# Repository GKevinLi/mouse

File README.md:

# Mouse: A custom wireless Bluetooth mouse

There is no cool name for it. I'm not good at naming things.

This is a wireless-capable Bluetooth mouse made entirely using custom parts. Everything required to make it is open source, and the files for each part are in their respective folders.
The only parts of this mouse that aren't custom are the battery and the various PCB attached components (switches, encoder, etc). 

This design can be used with any mouse switch, as long as it has dimensions of 12.8 x 5.8 x 6.5, and any 11mm mouse encoder. 6x6x7.3 silent switches theoretically should be able to work on this design as well, albeit with a few CAD modifications.

For more information on specific parts of the project, refer to the folder-specific READMEs in the cad, firmware, and pcb folders.\
CAD Readme: [Link](<https://github.com/GKevinLi/mouse/blob/main/cad/README.md>)\
Firmware Readme:  [Link](<https://github.com/GKevinLi/mouse/blob/main/firmware/README.md>)\
PCBs Readme:  [Link](<https://github.com/GKevinLi/mouse/blob/main/pcb/README.md>)

## Features

- PMW3610 Mouse Sensor
- nRF52833 Microcontroller
- Can be used when plugged in or on battery power
- Battery charging circuit
- Custom scroll wheel and mouse case
- 2 configurable side buttons

## Bill of Materials

| Item Name | Qty | Price (total) (USD) | Item link | Notes |
| --- | --- | --- | --- | --- |
| Mouse PCB, fully assembled | 2 | $150.05 | [Link](<https://jlcpcb.com/>) | this is how much it cost me for 5 PCBs, 2 fully assembled. Prices may vary. |
| PMW3610 | 1 | $1.09 | [Link](<https://www.aliexpress.us/item/3256809533648177.html?spm=a2g0o.productlist.main.7.117e61f1qj4GGu&algo_pvid=bf3782c9-0cfd-42bd-8a3f-8618d8d4e2c6&algo_exp_id=bf3782c9-0cfd-42bd-8a3f-8618d8d4e2c6-6&pdp_ext_f=%7B%22order%22%3A%22116%22%2C%22eval%22%3A%221%22%2C%22fromPage%22%3A%22search%22%7D&pdp_npi=6%40dis%21USD%214.53%211.09%21%21%214.53%211.09%21%402101e7a317932458066444948e0f08%2112000049947017292%21sea%21US%210%21ABX%211%210%21n_tag%3A-29910%3Bd%3A2859b2dd%3Bm03_new_user%3A-29895%3BpisId%3A5000000218152484&curPageLogUid=guoUMjTe3YSZ&utparam-url=scene%3Asearch%7Cquery_from%3A%7Cx_object_id%3A1005009719962929%7C_p_origin_prod%3A&_gl=1*7xkuy0*_gcl_au*MTIzNTAwODMyMy4xNzkzMjQ1ODEw*_ga*ODkxNjEwMTMuMTc5MzI0NTgxMg..*_ga_VED1YSGNC7*czE3OTMyNDU4MTEkbzEkZzAkdDE3OTMyNDU4MTEkajYwJGwwJGgw>) | this price is with the aliexpress welcome deal |
| Mouse Switch | 5 | $3.95 | [Link](<https://www.digikey.com/en/products/detail/aratas-formerly-omron-components-/D2FC-F-7N(60M)/20484328?gclsrc=aw.ds&gad_source=1&gad_campaignid=20509826117&gbraid=0AAAAADrbLlg5bJviKM8Id0HjudlkVKetQ&gclid=CjwKCAjwuobXBhBXEiwAYUaIlcOEJucEfbAOKAHeb95FXKGvGlaxJ1Z_NS2kmmfVS1ARsBkzc0fthhoCX_oQAvD_BwE>) | Any 12.8x5.8x6.5 mouse switch works, you can buy them or take them off old mice |
| 11mm Mouse Encoder | 1 | $9.39 | [Link](<https://www.amazon.com/dp/B07HCFMQ3X?plpRedirect=mhFallback&ref=clp_hp_h_pc>) | Any 11mm mouse encoder works, you can buy them or take them off old mice |
| 602535 Battery | 1 | $7.99 | [Link](<https://www.amazon.com/dp/B0GWCRMPSY?plpRedirect=mhFallback&ref=clp_hp_h_pc>) | Any 602535 battery works here. |
| **Total Price (USD)** | | **$172.47** | | |

To build the mouse fully, you will need a soldering iron (and some soldering experience), an SWD debugger, and access to a 3D printer. The links given in the BOM are just recommendations. The battery is optional and the mouse can be used via USB power without it.

## Building tips / Notes:
- This project is currently in a very early stage of development, so building this is not recommended at this time. Only try to build this yourself if you REALLY know what you are doing. It is possible that your project may not work due to some oversight I haven't found yet.
- I am a very busy college student so updates on this may be slow.
- There are probably many issues with this design that I have not discovered yet. Documented issues will be in the folder-specific READMEs.
- The current board design has several major issues. These will have to either be fixed in KiCad or by modifying the assembled board. A corrected version of the design will be made.... eventually, but for now I have documented the issues in the PCB folder's readme file.
- The current mouse case does not have side buttons. These will be added later as well.
- The current mouse case does not support mouse skates.
- To build this, you will have to order your own boards from JLCPCB or another PCB manufacturer. Instructions for this will not be provided at the moment, since the board design has issues anyway. If you have enough experience to fix them then you probably have enough experience to order the boards by yourself as well.
- There is currently not a lot of documentation on this project. This is just a fun personal project of mine at the moment, and I do not have that much time to consistently work on it. I will update this in the future, though.
- THIS IS NOT (currently) A GOOD MOUSE. Do not expect this project, in its current form, to be better than whatever mouse you personally own.

## Credits:
https://github.com/badjeff/leylabella for CAD references

https://github.com/siderakb/pmw3610-pcb for a PMW3610 schematic reference

https://github.com/wareya/DIY-Gaming-Mouse for PCB design and CAD references

KiCanvas PCB Link Here:

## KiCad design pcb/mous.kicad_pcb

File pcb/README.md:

# Wireless Mouse PCB README

This is the README for the project's PCB and KiCad files. Relevant information and known issues will be documented here.
An update will be coming soon to fix the current issues.

## Known Issues: 
- VBus Pin not connected to 5V, making USB flash not work on this version of the PCB. If ordering this board, this is the #1 thing that needs to be fixed in KiCad.
- GND and SCROLL_A are swapped on the encoder footprint
- NRESET pin, when connected to the nRF52833, causes erratic sensor issues on the PMW3610. The recommended solution for this is to either disconnect it from the microcontroller entirely, as it is not used, or physically cut the trace with a knife.

## Future Improvements:

I am planning on creating a second iteration of this PCB with some new features:
- Upgrade to nRF52840 chip
- Potential better mouse sensor
- Integrated battery charging IC
- LEDs
- Move ON/OFF switch to bottom for easier accessibility

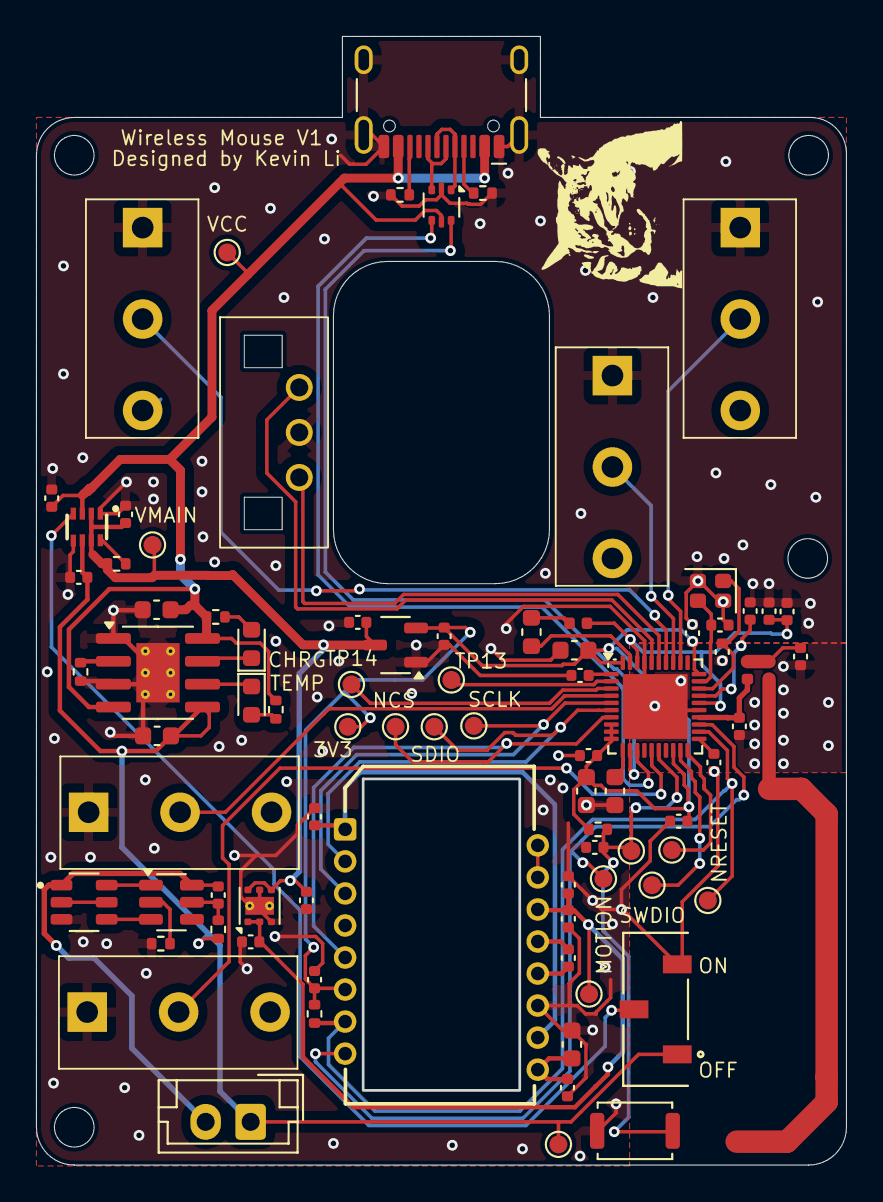
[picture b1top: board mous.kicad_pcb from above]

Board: 4 copper layers, 45.0 x 62.7 mm, 84 parts (0 on the bottom side), 58 nets.

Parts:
C1, C3: 10nf; C_0402_1005Metric
C2, C33, C34: 10uf; C_0603_1608Metric
C4, C5, C6, C11, C12, C19, C27, C28: 100nf; C_0402_1005Metric
C7: 3.3uf; C_0402_1005Metric
C8, C9, C10, C16, C25, C26, C30, C31: 1uf; C_0402_1005Metric
C13, C14, C15: 4.7uf; C_0603_1608Metric
C17: 47nf; C_0402_1005Metric
C18: 820pf; C_0402_1005Metric
C20: 100pf; C_0402_1005Metric
C21: 1pf; C_0402_1005Metric
C22: 1.2pf; C_0402_1005Metric
C23, C24: 12pf; C_0402_1005Metric
C32: 2.2uf; C_0402_1005Metric
D4, D5: LED; LED_0603_1608Metric
IC2: LM66200DRLR; SOT8
J1: USB_C_Receptacle_USB2.0_14P; USB_C_Receptacle_HCTL_HC-TYPE-C-16P-01A
J3: Screw_Terminal_01x02; JST_EH_B2B-EH-A_1x02_P2.50mm_Vertical
L1: 10uH; L_0603_1608Metric
L2: 15nH; L_0402_1005Metric
L3: 4.7nH; L_0402_1005Metric
L4: 2.2nH; L_0402_1005Metric
Q1: FS8205; SOT95P280X145-6N
R1, R8, R29: 10k; R_0402_1005Metric
R3: 100; R_0402_1005Metric
R4, R9, R10: 1k; R_0402_1005Metric
R5, R6: 5k1; R_0402_1005Metric
R11: 5.1k; R_0402_1005Metric
SW1, SW2, SW4, SW6, SW7: SW_SPDT_312; MOYUS SWITCXH
SW3: RotaryEncoder; MOUS WHEL
SW5: SW_SPDT; SW_JS102011JCQN
SW8: SW_Push; SW_Push_SPST_NO_Alps_SKRK
TP1, TP2, TP3, TP4, TP5, TP6, TP7, TP8, TP9, TP10, TP11, TP12, TP13, TP14: TestPoint; TestPoint_Pad_D1.0mm
U1: PMW3610; PMW3610DM-SUDU 16Pin
U2: TLV76718DRVx; WSON-6-1EP_2x2mm_P0.65mm_EP1x1.6mm_ThermalVias
U4: USBLC6-2P6; SOT-666
U5: DW01A; SOT-23-6
U6: TP4056-42-ESOP8; SOIC-8-1EP_3.9x4.9mm_P1.27mm_EP2.41x3.3mm_ThermalVias
U7: XC6206PxxxMR; SOT-23-3
U8: nRF52833_QDxx; QFN-40-1EP_5x5mm_P0.4mm_EP3.6x3.6mm
VMAIN: TestPoint; TestPoint_Pad_D1.0mm
Y2: Crystal_GND24; Crystal_SMD_2016-4Pin_2.0x1.6mm

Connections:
+1V8: C6.1, C7.1, C9.1, TP12.1, U1.14 (VDD), U2.1 (OUT), U2.2 (SNS)
+3.3V: C5.1, C10.1, C11.1, C12.1, C13.1, C14.1, C26.1, R1.1, R29.2, TP11.1, U1.6 (VDDIO), U7.2 (VO), U8.8 (VDD), U8.9 (VDDH), U8.10 (VBUS), U8.18 (VDD), U8.30 (VDD), U8.40 (VDD)
BAT-: C27.2, J3.2, Q1.1, U5.6 (GND)
D+: U4.4 (I/O2), U8.13 (D+)
D-: U4.6 (I/O1), U8.12 (D-)
GND: C1.2, C2.2, C3.2, C5.2, C6.2, C7.2, C8.2, C9.2, C10.2, C11.2, C12.2, C13.2, C14.2, C15.2, C16.2, C17.2, C18.2, C19.2, C20.2, C21.2, C22.2, C23.2, C24.2, C25.2, C26.2, C28.2, C30.2, C31.2, C32.2, C33.2, C34.2, IC2.1 (GND@1), IC2.5 (GND@2), J1.A1 (GND), J1.A12 (GND), J1.B1 (GND), J1.B12 (GND), J1.S1 (SHIELD), Q1.3, R4.2, R5.2, R6.2, R11.2, SW1.1 (B), SW2.1 (B), SW3.C, SW4.1 (B), SW5.3 (C), SW6.1 (B), SW7.1 (B), SW8.1, U1.11 (GND), U2.3 (GND), U2.5 (GND), U2.7 (PAD), U4.2 (GND), U6.1 (TEMP), U6.3 (GND), U6.9 (EPAD), U7.1 (GND), U8.25 (VSS_PA), U8.37 (VSS), U8.41 (VSS), Y2.2, Y2.4
MOTION: TP7.1, U1.8 (MOTION), U8.23 (NFC2/P0.10)
MOUSE1: SW1.3 (A), U8.34 (AIN5/P0.29)
MOUSE2: SW2.3 (A), U8.32 (AIN0/P0.02)
MOUSE_MID: SW4.3 (A), U8.33 (AIN4/P0.28)
MOUSE_SIDE: SW6.3 (A), U8.4 (AIN2/P0.04)
MOUSE_SIDE_2: SW7.3 (A), U8.15 (P0.17)
NCS: TP6.1, U1.5 (NCS), U8.7 (P0.11)
NRESET: R1.2, TP8.1, U1.7 (NRESET), U8.22 (NFC1/P0.09)
unnamed: C22.1, L3.1, L4.2
unnamed: D4.2 (A), R9.2
unnamed: D4.1 (K), U6.6 (~STDBY)
unnamed: D5.2 (A), R10.2
unnamed: D5.1 (K), U6.7 (~CHRG)
unnamed: IC2.8 (ST), R8.2
unnamed: J1.A5 (CC1), R6.1
unnamed: J1.B5 (CC2), R5.1
unnamed: J1.A6 (D+), J1.B6 (D+), U4.3 (I/O2)
unnamed: J1.A7 (D-), J1.B7 (D-), U4.1 (I/O1)
unnamed: L1.1, L2.2
unnamed: Q1.2, Q1.5
unnamed: C3.1, U1.1 (+VCSEL), U1.10 (PASS_T)
unnamed: U1.15 (XYLASER), U1.16 (-VCSEL)
unnamed: C4.2, U1.13 (CN)
unnamed: C4.1, U1.12 (CP)
unnamed: C1.1, C2.1, U1.9 (VCP)
unnamed: R4.1, U5.2 (CS)
unnamed: Q1.4, U5.3 (OC)
unnamed: Q1.6, U5.1 (OD)
unnamed: C27.1, R3.2, U5.5 (VCC)
unnamed: R11.1, U6.2 (PROG)
unnamed: C21.1, L3.2, U8.24 (ANT)
unnamed: L1.2, U8.39 (DCC)
unnamed: C19.1, U8.1 (DEC1)
unnamed: C20.1, U8.27 (DEC3)
unnamed: C16.1, C17.1, L2.1, U8.26 (DEC6), U8.38 (DEC4)
unnamed: C18.1, U8.21 (DEC5)
unnamed: C15.1, U8.11 (DECUSB)
unnamed: C24.1, U8.28 (XC1), Y2.1
unnamed: C23.1, U8.29 (XC2), Y2.3
unnamed: TP13.1, U8.2 (XL1/P0.00)
unnamed: TP14.1, U8.3 (XL2/P0.01)
ON: IC2.4 (ON), SW5.2 (B)
P0.18: C28.1, R29.1, SW8.2, TP2.1, U8.16 (P0.18/~RESET)
SCLK: TP4.1, U1.3 (SCLK), U8.5 (AIN3/P0.05)
SCROLL_A: SW3.A, U8.36 (AIN7/P0.31)
SCROLL_B: SW3.B, U8.35 (AIN6/P0.30)
SDIO: TP5.1, U1.2 (SDIO), U8.6 (P1.09)
SWDCLK: TP3.1, U8.20 (SWDCLK)
SWDIO: TP1.1, U8.19 (SWDIO)
VBAT: C31.1, C34.1, IC2.6 (VIN2), J3.1, R3.1, SW5.1 (A), TP10.1, U6.5 (BAT)
VCC: C30.1, C33.1, IC2.3 (VIN1), J1.A4 (VBUS), J1.A9 (VBUS), J1.B4 (VBUS), J1.B9 (VBUS), R9.1, R10.1, TP9.1, U4.5 (VBUS), U6.4 (V_{CC}), U6.8 (CE)
V_MAIN: C8.1, C25.1, C32.1, IC2.2 (VOUT@1), IC2.7 (VOUT@2), R8.1, U2.4 (EN), U2.6 (IN), U7.3 (VI), VMAIN.1

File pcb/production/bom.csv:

Designator,Footprint,Quantity,Value,LCSC Part #
"C1, C3",0402,2,10nf,
"C10, C16, C25, C26, C30, C31, C8, C9",0402,8,1uf,
"C11, C12, C19, C27, C28, C4, C5, C6",0402,8,100nf,
"C13, C14, C15",0603,3,4.7uf,
C17,0402,1,47nf,
C18,0402,1,820pf,
"C2, C33, C34",0603,3,10uf,
C20,0402,1,100pf,
C21,0402,1,1pf,
C22,0402,1,1.2pf,
"C23, C24",0402,2,12pf,
C32,0402,1,2.2uf,
C7,0402,1,3.3uf,
"D4, D5",0603,2,LED,
IC2,SOT8,1,LM66200DRLR,
J1,USB_C_Receptacle_HCTL_HC-TYPE-C-16P-01A,1,USB_C_Receptacle_USB2.0_14P,
J3,JST_EH_B2B-EH-A_1x02_P2.50mm_Vertical,1,Screw_Terminal_01x02,
L1,0603,1,10uH,
L2,0402,1,15nH,
L3,0402,1,4.7nH,
L4,0402,1,2.2nH,
Q1,SOT95P280X145-6N,1,FS8205,
"R1, R29, R8",0402,3,10k,
"R10, R4, R9",0402,3,1k,
R11,0402,1,5.1k,
R3,0402,1,100,
"R5, R6",0402,2,5k1,
"SW1, SW2, SW4, SW6, SW7",MOYUS SWITCXH,5,SW_SPDT_312,
SW3,MOUS WHEL,1,RotaryEncoder,
SW5,SW_JS102011JCQN,1,SW_SPDT,
SW8,SW_Push_SPST_NO_Alps_SKRK,1,SW_Push,
"TP1, TP10, TP11, TP12, TP13, TP14, TP2, TP3, TP4, TP5, TP6, TP7, TP8, TP9, VMAIN",TestPoint_Pad_D1.0mm,15,TestPoint,
U1,PMW3610DM-SUDU 16Pin,1,PMW3610,
U2,WSON-6-1EP_2x2mm_P0.65mm_EP1x1.6mm_ThermalVias,1,TLV76718DRVx,
U4,SOT-666,1,USBLC6-2P6,
U5,SOT-23-6,1,DW01A,
U6,SOIC-8-1EP_3.9x4.9mm_P1.27mm_EP2.41x3.3mm_ThermalVias,1,TP4056-42-ESOP8,
U7,SOT-23-3,1,XC6206PxxxMR,
U8,QFN-40-1EP_5x5mm_P0.4mm_EP3.6x3.6mm,1,nRF52833_QDxx,
Y2,Crystal_SMD_2016-4Pin_2.0x1.6mm,1,Crystal_GND24,

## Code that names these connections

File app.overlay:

/ {

	custom {
		compatible = "gpio-leds";
		cs: cs_pin {
			gpios = <&gpio0 17 GPIO_ACTIVE_LOW>;
		};

		motion: motion_pin {
			gpios = <&gpio0 10 (GPIO_PULL_UP | GPIO_ACTIVE_LOW)>;
		};

		sdio: sdio_pin {
			gpios = <&gpio0 0 GPIO_ACTIVE_HIGH>;
		};

		sclk: sclk_pin {
			gpios = <&gpio0 1 GPIO_ACTIVE_HIGH>;
		};

		scroll_a: scroll_a_pin {
			gpios = <&gpio0 30 GPIO_ACTIVE_HIGH>;
		};

		scroll_b: scroll_b_pin {
			gpios = <&gpio0 9 GPIO_ACTIVE_HIGH>;
		};


		side_button_1: side_button_1_pin {
			gpios = <&gpio0 4 (GPIO_PULL_UP | GPIO_ACTIVE_LOW)>;
		};

		side_button_2: side_button_2_pin {
			gpios = <&gpio0 20 (GPIO_PULL_UP | GPIO_ACTIVE_LOW)>;

		};




	};

	buttons {
		compatible = "gpio-keys";

		button0: button_0 {
			gpios = <&gpio0 29 (GPIO_PULL_UP | GPIO_ACTIVE_LOW)>;
			label = "Push button switch 0";
			zephyr,code = <INPUT_KEY_0>;
		};

		button1: button_1 {
			gpios = <&gpio0 2 (GPIO_PULL_UP | GPIO_ACTIVE_LOW)>;
			label = "Push button switch 1";
			zephyr,code = <INPUT_KEY_1>;
		};

		button2: button_2 {
			gpios = <&gpio0 28 (GPIO_PULL_UP | GPIO_ACTIVE_LOW)>;
			label = "Push button switch 2";
			zephyr,code = <INPUT_KEY_2>;
		};

	};

	aliases {

		sw4 = &button4;

	};


};

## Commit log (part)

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2026-05-27 Initial commit for MOUSE
